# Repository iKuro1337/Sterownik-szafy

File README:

Sterownik oświetlenia w szafie oraz przejścia obok szafy

BOM płytka bazowa:
8x rezystor 10k
8x rezystor 60
8x IRLZ44N
8x złącza ARK 2pin
nx Listwy goldpin

BOM płytka sterująca Atmega32:
1x Atmega32
2x Zworka
1x Przycisk monostabilny
1x złącze ARK 2pin
4x kondensator 100n
1x rezystor 10k
1x rezystor pod diode (ok 200)
nx listwy goldpin

BOM obudowa:
3x JACK stereo (2 mogą być MONO)
1x wyświetlacz 4x20 z przetwornikiem i2c
1x czujnik ruchu PIR 5V HC-SR501
WIP czujnik oświetlenia.

Błędy (v1)
1) Odwrócone piny zasilające płytkę bazową 5V i 12V - jest 12V po lewej, 5V po prawej, ma być 5V po lewej, 12 po prawej (płytka Atmega32)
2) Za duży odstęp między pinami 12V,5V i GND wyprowadzonymi na płytce bazowej (płytka bazowa)
3) Za wąskie ścieżki zasilania - należy je pogrubić (wszystko)
4) Pady z przycisku stykają się z ramką płytki (płytka Atmega32)
5) Brak złącza na zasilanie/zasilacz poza obudową (obudowa)
6) Źle podłączane zasilanie - osobna płytka nie ma miejsca do trwałego umiejscowienia.

Podłączenie:
- Wyświetlacz 4x20 podpiąć pod piny 22 i 23 Atmega 32 bezpośrednio. Zasilanie wziąć z wyprowadzeń
- Zworkę podświetlenia wyświetlacza zastąpić przyciskiem kołyskowym bądź innym, spełniającym funkcję włączania/wyłączania podświetlenia.
- Oświetlenie jest podłączane do kolejnych złącz ARK na dowolnej zasadzie.
- Podłączenie czujnika ruchu PIR tylko i wyłącznie na pin 1 - wpinany na pojedyncze gniazdo JACK
- Podłączenie czujników otwarcia/zamknięcia strony szafy podłączyć do pinów 2 i 3, drugą stronę złączyć z masą - wpinane na wybrane jedno z dwóch gniazd JACK
- Poszczególne gniazda mają następujące funkcje (od prawej góry, dołu, do lewej strony dołu)
  1) Światło zewnętrzne zapalające się zawsze jak jest ruch
  2) Światło wewnętrzne szafy, góra, zapalająca się kiedy którekolwiek z drzwi jest otwarte
  3) Światło wewnętrzne szafy, lewa strona, zapalająca się kiedy lewe drzwi są otwarte
  4) Światło wewnętrzne szafy, lewa strona, zapalająca się kiedy lewe drzwi są otwarte
  5) Światło wewnętrzne szafy, prawa strona, zapalająca się kiedy prawe drzwi są otwarte
  6) Światło wewnętrzne szafy, prawa strona, zapalająca się kiedy prawe drzwi są otwarte
  7) Światło wewnętrzne szafy, prawa strona, zapalająca się kiedy prawe drzwi są otwarte
  8) Światło wewnętrzne szafy, prawa strona, zapalająca się kiedy prawe drzwi są otwarte
- Płytkę zasilającą ustawiamy na 5V, przylutowujemy do niej 4 kable (po poprawce) bądź 6 kabli (przed korektą) skręconą parę czerwony/czarny podpinamy od strony zasilania płytki. Dodatkowy przewód od strony +12V podłączany jest po prawej stronie płytki bazowej. przewód czerwony podłączamy po prawej stronie trójki pinów zasilających. przewód czerwony ma być podpięty po lewej stronie płytki.

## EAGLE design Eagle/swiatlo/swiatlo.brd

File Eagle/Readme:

Pliki Eagle

Światło - plik z płytką bazową do której podpinane są wszystkie elementy
Atmega32 - plik z płytką sterującą na bazie Atmega32. do niej podpinane jest zasilanie, programator. Płytka jest osadzana na płytce bazowej

Do dodania
Płytka na bazie ESP8266

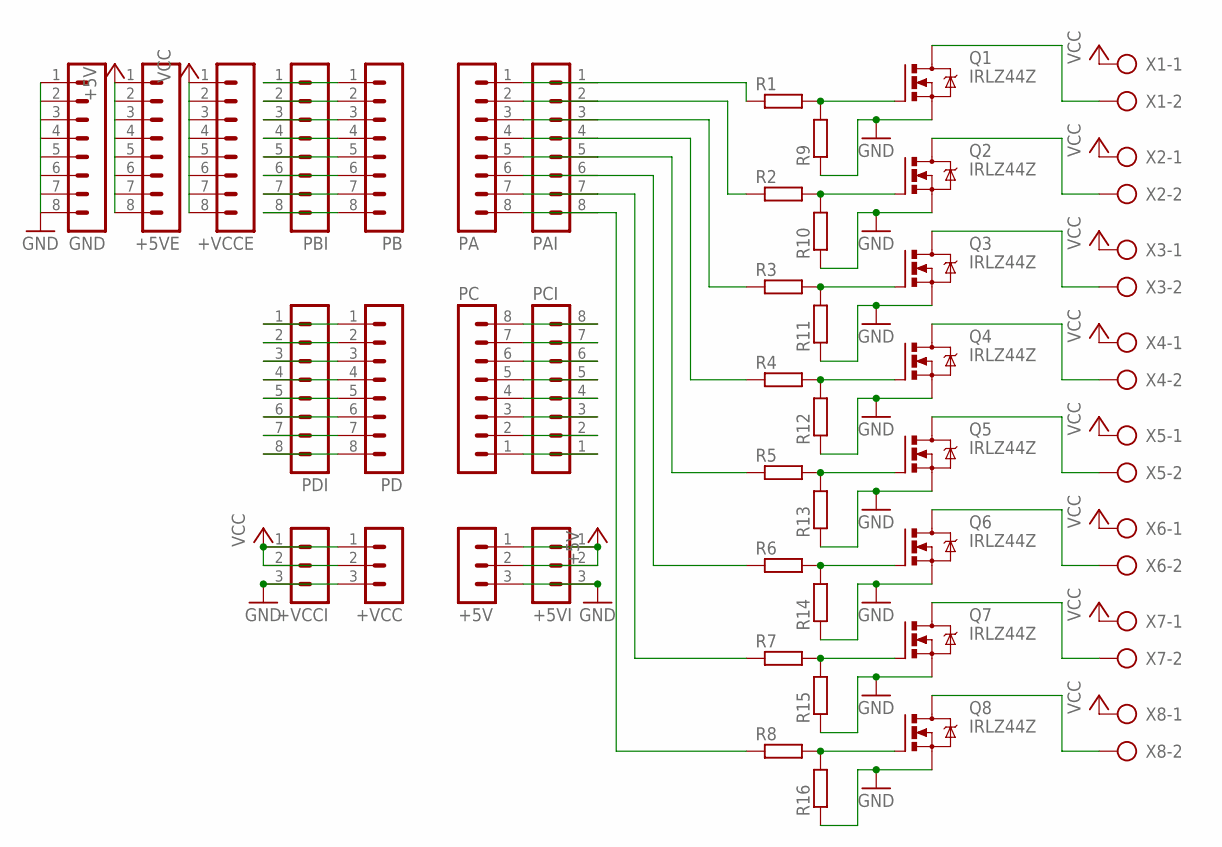
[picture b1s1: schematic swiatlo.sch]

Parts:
+5V, +5VI: MA03-1
+5VE: MA08-1
+VCC: MA03-1
+VCCE: MA08-1
+VCCI: MA03-1
GND: MA08-1
PA: MA08-1
PAI: MA08-1
PB: MA08-1
PBI: MA08-1
PC: MA08-1
PCI: MA08-1
PD: MA08-1
PDI: MA08-1
Q1, Q2, Q3, Q4, Q5, Q6, Q7, Q8: IRLZ44Z; TO220BH
R1, R2, R3, R4, R5, R6, R7, R8, R9, R10, R11, R12, R13, R14, R15, R16: R-EU_0204/7; 0204/7
X1, X2, X3, X4, X5, X6, X7, X8: AK300/2

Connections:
+5V: +5V.1, +5V.2, +5VE.1, +5VE.2, +5VE.3, +5VE.4, +5VE.5, +5VE.6, +5VE.7, +5VE.8, +5VI.1, +5VI.2
GND: +5V.3, +5VI.3, +VCC.3, +VCCI.3, GND.1, GND.2, GND.3, GND.4, GND.5, GND.6, GND.7, GND.8, Q1.S, Q2.S, Q3.S, Q4.S, Q5.S, Q6.S, Q7.S, Q8.S, R9.1, R10.1, R11.1, R12.1, R13.1, R14.1, R15.1, R16.1
unnamed: Q1.G, R1.2, R9.2
unnamed: Q2.G, R2.2, R10.2
unnamed: Q3.G, R3.2, R11.2
unnamed: Q4.G, R4.2, R12.2
unnamed: Q5.G, R5.2, R13.2
unnamed: Q6.G, R6.2, R14.2
unnamed: Q7.G, R7.2, R15.2
unnamed: Q8.G, R8.2, R16.2
unnamed: Q1.D, X1.2
unnamed: Q2.D, X2.2
unnamed: Q3.D, X3.2
unnamed: Q4.D, X4.2
unnamed: Q5.D, X5.2
unnamed: Q6.D, X6.2
unnamed: Q7.D, X7.2
unnamed: Q8.D, X8.2
unnamed: PC.8, PCI.8
unnamed: PC.7, PCI.7
unnamed: PC.6, PCI.6
unnamed: PC.5, PCI.5
unnamed: PC.4, PCI.4
unnamed: PC.3, PCI.3
unnamed: PC.2, PCI.2
unnamed: PC.1, PCI.1
unnamed: PA.1, PAI.1, R1.1
unnamed: PA.2, PAI.2, R2.1
unnamed: PA.3, PAI.3, R3.1
unnamed: PA.4, PAI.4, R4.1
unnamed: PA.5, PAI.5, R5.1
unnamed: PA.6, PAI.6, R6.1
unnamed: PA.7, PAI.7, R7.1
unnamed: PA.8, PAI.8, R8.1
unnamed: PD.8, PDI.8
unnamed: PD.7, PDI.7
unnamed: PD.6, PDI.6
unnamed: PD.5, PDI.5
unnamed: PD.4, PDI.4
unnamed: PD.3, PDI.3
unnamed: PD.2, PDI.2
unnamed: PD.1, PDI.1
unnamed: PB.8, PBI.8
unnamed: PB.7, PBI.7
unnamed: PB.6, PBI.6
unnamed: PB.5, PBI.5
unnamed: PB.4, PBI.4
unnamed: PB.3, PBI.3
unnamed: PB.2, PBI.2
unnamed: PB.1, PBI.1
VCC: +VCC.1, +VCC.2, +VCCE.1, +VCCE.2, +VCCE.3, +VCCE.4, +VCCE.5, +VCCE.6, +VCCE.7, +VCCE.8, +VCCI.1, +VCCI.2, X1.1, X2.1, X3.1, X4.1, X5.1, X6.1, X7.1, X8.1

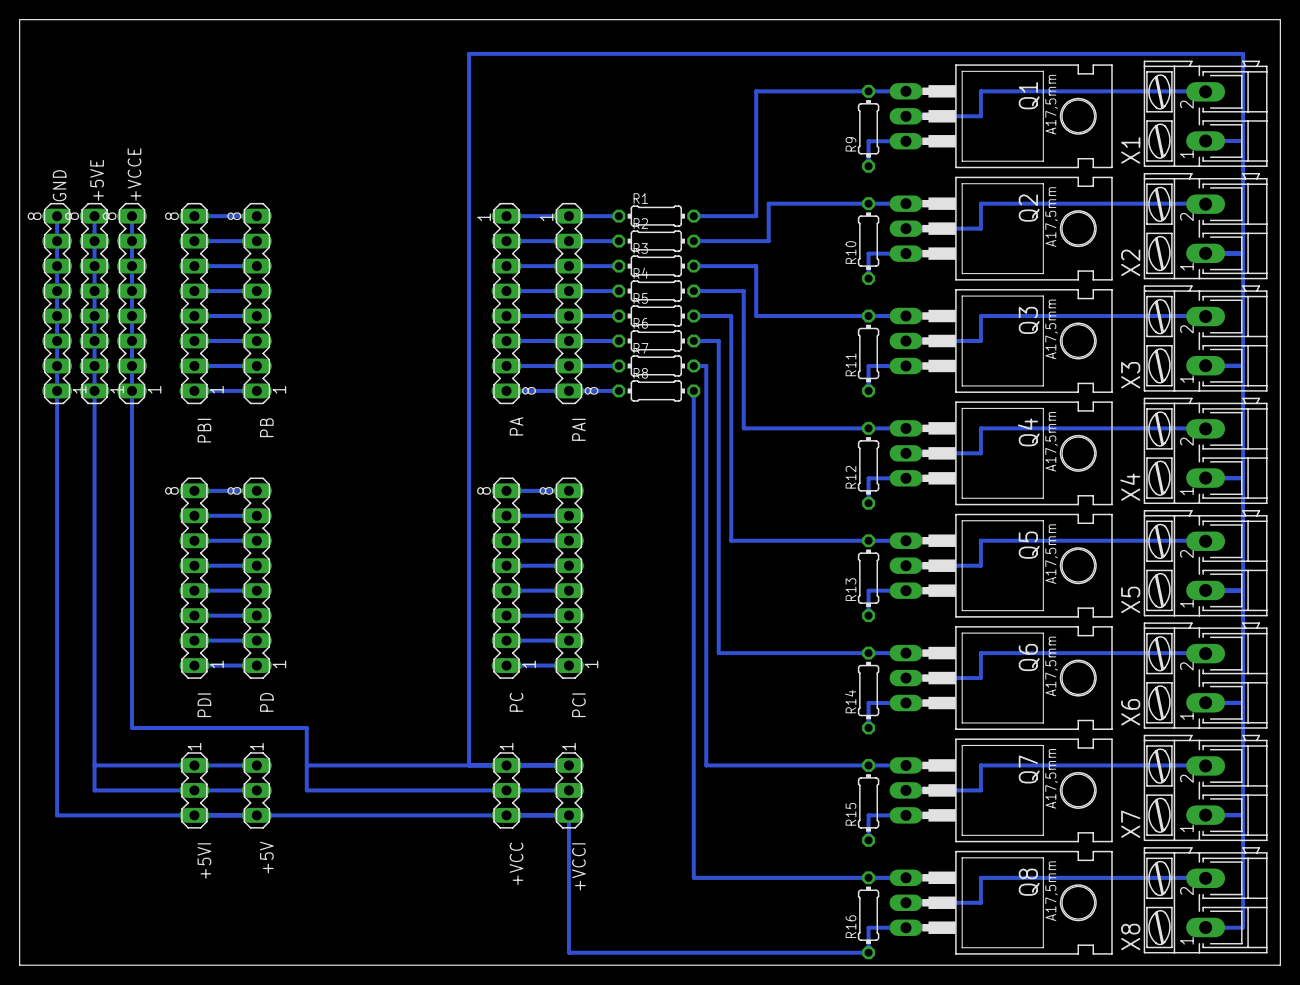
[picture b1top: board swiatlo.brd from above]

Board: 2 copper layers, 128.2 x 96.2 mm, 47 parts (0 on the bottom side), 51 nets.

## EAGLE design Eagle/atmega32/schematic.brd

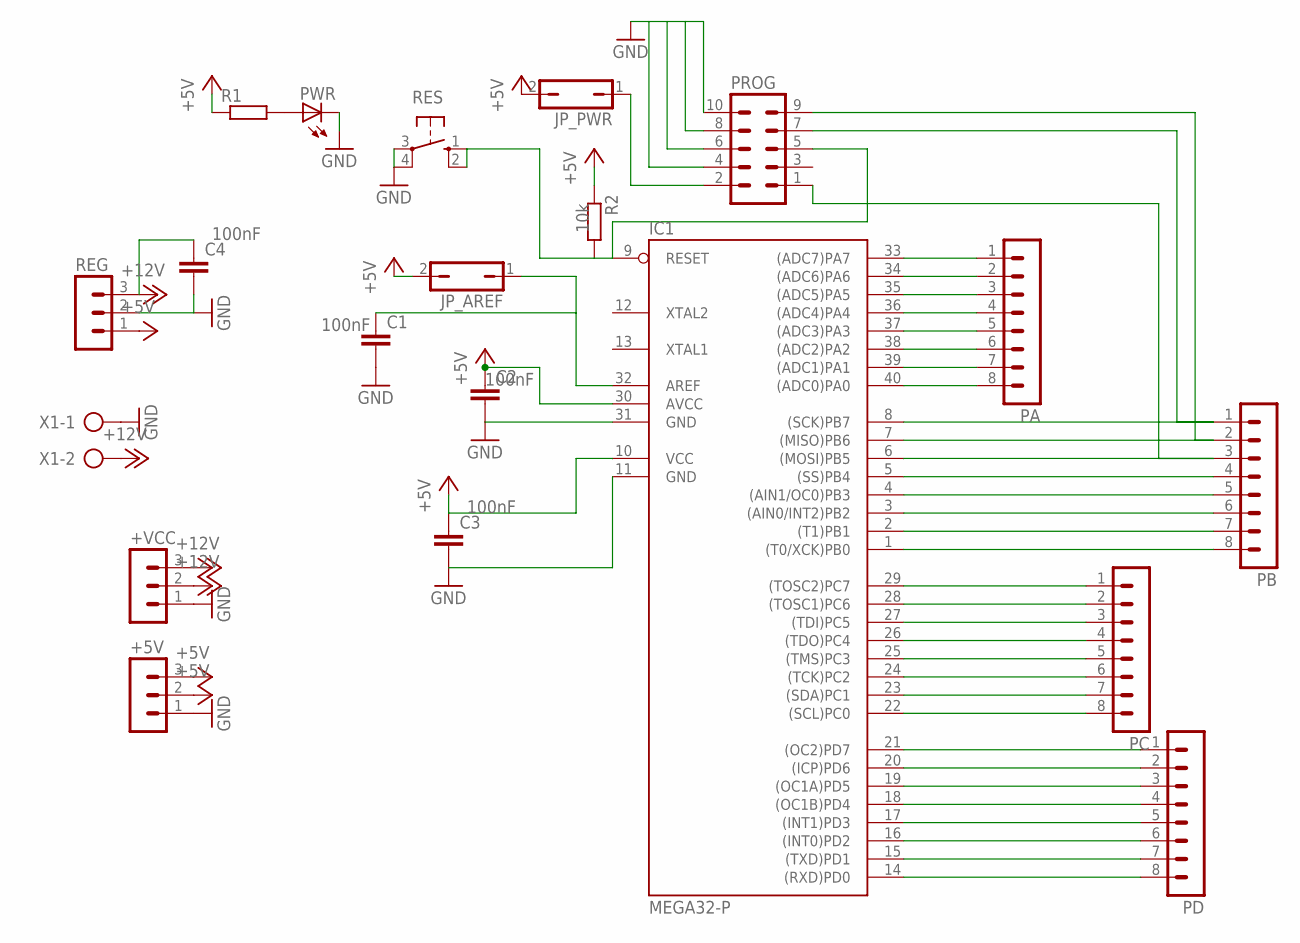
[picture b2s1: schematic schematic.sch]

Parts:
+5V: MA03-1
+VCC: MA03-1
C1, C2, C3, C4: C2,5-3; C2.5-3
IC1: MEGA32-P; DIL40
JP_AREF: JP1Q; JP1
JP_PWR: JP1Q; JP1
PA: MA08-1
PB: MA08-1
PC: MA08-1
PD: MA08-1
PROG: MA05-2
PWR: LED_E; LED_1206
R1, R2: RR1206; R1206
REG: MA03-1
RES: 10-XX; B3F-10XX
X1: AK300/2

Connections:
+5V: +5V.2, +5V.3, C2.1, C3.1, IC1.10 (VCC), IC1.30 (AVCC), JP_AREF.2, JP_PWR.2, R1.1, R2.1, REG.1
+12V: +VCC.2, +VCC.3, C4.1, REG.3, X1.2
GND: +5V.1, +VCC.1, C1.2, C2.2, C3.2, C4.2, IC1.11 (GND), IC1.31 (GND), PROG.4, PROG.6, PROG.8, PROG.10, PWR.C, REG.2, RES.3, RES.4 (P1), X1.1
unnamed: IC1.21 ((OC2)PD7), PD.1
unnamed: IC1.20 ((ICP)PD6), PD.2
unnamed: IC1.19 ((OC1A)PD5), PD.3
unnamed: IC1.18 ((OC1B)PD4), PD.4
unnamed: IC1.17 ((INT1)PD3), PD.5
unnamed: IC1.16 ((INT0)PD2), PD.6
unnamed: IC1.15 ((TXD)PD1), PD.7
unnamed: IC1.14 ((RXD)PD0), PD.8
unnamed: IC1.29 ((TOSC2)PC7), PC.1
unnamed: IC1.28 ((TOSC1)PC6), PC.2
unnamed: IC1.27 ((TDI)PC5), PC.3
unnamed: IC1.26 ((TDO)PC4), PC.4
unnamed: IC1.25 ((TMS)PC3), PC.5
unnamed: IC1.24 ((TCK)PC2), PC.6
unnamed: IC1.23 ((SDA)PC1), PC.7
unnamed: IC1.22 ((SCL)PC0), PC.8
unnamed: IC1.8 ((SCK)PB7), PB.1, PROG.7
unnamed: IC1.7 ((MISO)PB6), PB.2, PROG.9
unnamed: IC1.6 ((MOSI)PB5), PB.3, PROG.1
unnamed: IC1.5 ((SS)PB4), PB.4
unnamed: IC1.4 ((AIN1/OC0)PB3), PB.5
unnamed: IC1.3 ((AIN0/INT2)PB2), PB.6
unnamed: IC1.2 ((T1)PB1), PB.7
unnamed: IC1.1 ((T0/XCK)PB0), PB.8
unnamed: IC1.33 ((ADC7)PA7), PA.1
unnamed: IC1.34 ((ADC6)PA6), PA.2
unnamed: IC1.35 ((ADC5)PA5), PA.3
unnamed: IC1.36 ((ADC4)PA4), PA.4
unnamed: IC1.37 ((ADC3)PA3), PA.5
unnamed: IC1.38 ((ADC2)PA2), PA.6
unnamed: IC1.39 ((ADC1)PA1), PA.7
unnamed: IC1.40 ((ADC0)PA0), PA.8
unnamed: IC1.9 (RESET), PROG.5, R2.2, RES.1 (S), RES.2 (S1)
unnamed: C1.1, IC1.32 (AREF), JP_AREF.1
unnamed: JP_PWR.1, PROG.2
unnamed: PWR.A, R1.2

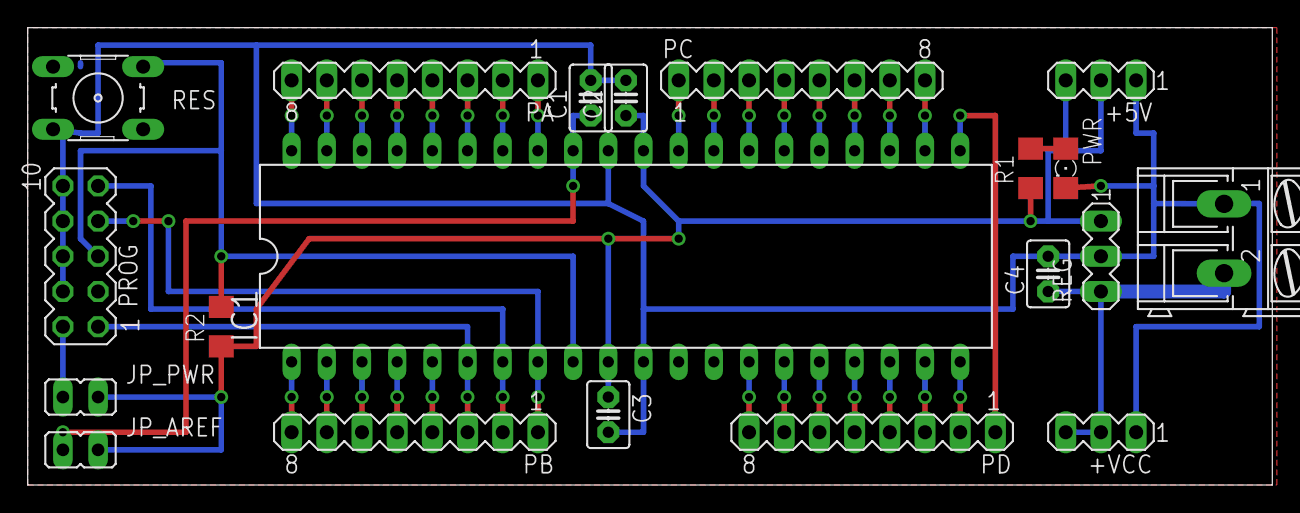
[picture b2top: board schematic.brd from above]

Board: 2 copper layers, 89.8 x 33.0 mm, 20 parts (0 on the bottom side), 39 nets.

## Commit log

2016-07-29 Readme sterownika szafy
    W tym readme zawarte będą wszystkie niezbędne informacje
2016-07-29 Pliki Eagle
